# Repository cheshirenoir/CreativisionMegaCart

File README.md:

# CreativisionMegaCart
NOTE: THIS IS NOT COMPATIBLE WITH THE CREATIVISION II WITHOUT MODIFICATION!
(See: http://www.madrigaldesign.it/forum/viewtopic.php?f=10&t=330&p=3201#p3201 )

Multiple ROM Cartridge system for the VTech Creativision, AKA the Dick Smith Wizzard

This is a project I’ve been working on for a while and today I’m pleased to announce the release of our open Source MultiCart system.

Clockmeister kindly gave me all the information from his cart, and gave me permission to release this as Open Source. We both also want to acknowledge and thank the great people over at the Madrigal Design Creativision forums for all their help as well.

My minor contribution was taking the design and putting it in KiCad. I had to spend a bit of time debugging, but Clockmeister assisted above and beyond the call of duty.

This design is released under a CC-BY-SA license. Remix, but always share!

I won’t include ROMs for copyright reasons but they are quite easy to locate on the net if you search around. Note: If you want to program your own EPROM, I understand you have to split the 32K image into two 16K files and then swap the first 16K with the second 16K and re-join them. Clockmeister suggests WinHEX for this.

Parts list is as follows:
1 x 27C801 EPROM (or equivalent)
1 x 0.1uF Ceramic disk capacitor
2 x 1N1418 diode (or equivalent)
1 x DIP switch block (5 switches)
1 x 6 way 4.7kΩ resistor block. (Don’t do what I did and order the 5 way because you counted the pins. It should have seven pins)

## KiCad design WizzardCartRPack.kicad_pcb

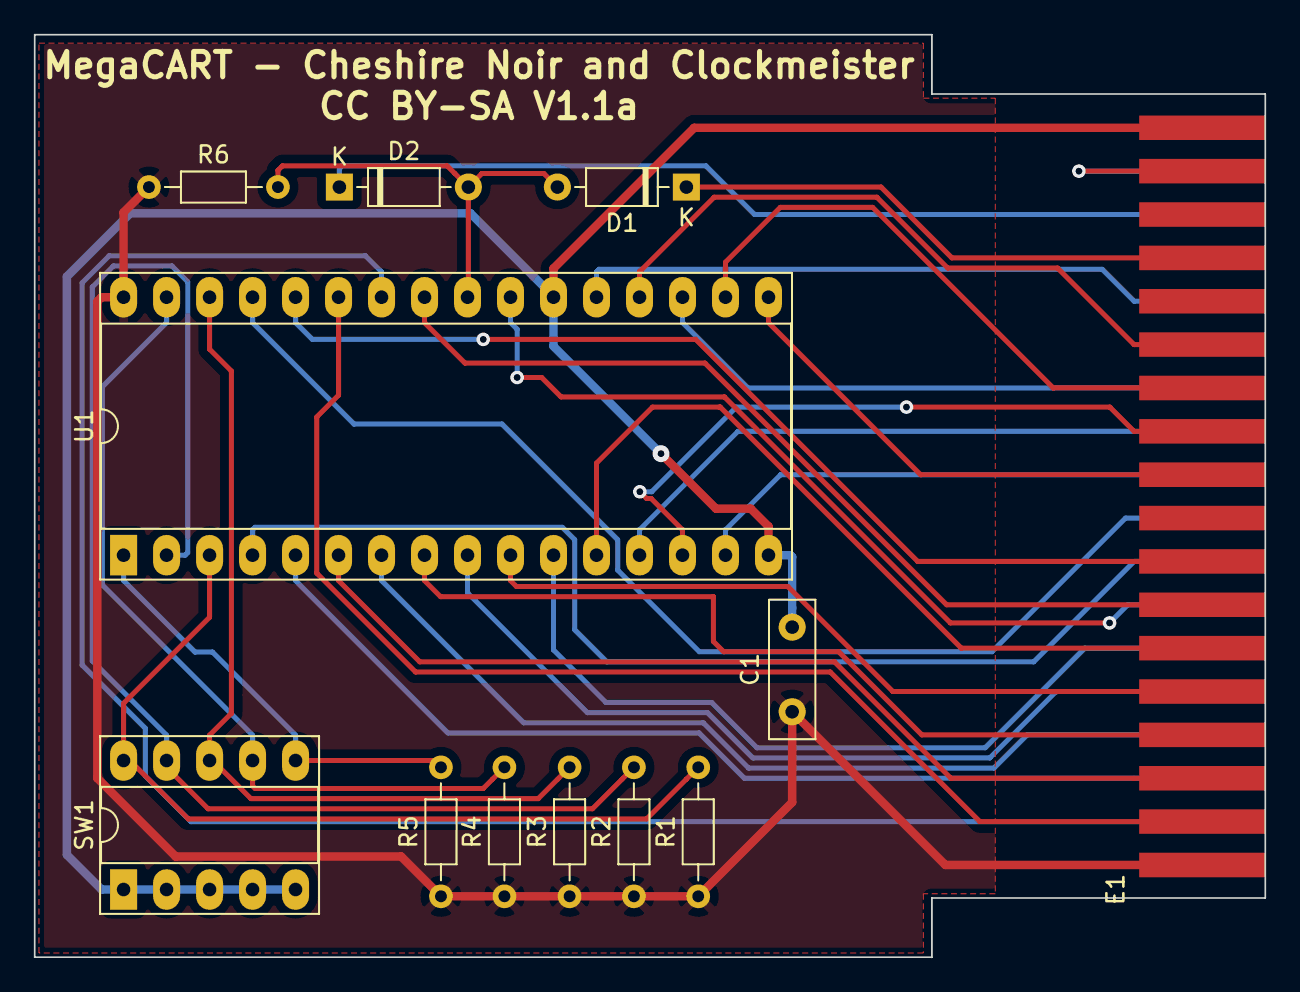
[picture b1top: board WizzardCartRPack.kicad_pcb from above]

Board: 2 copper layers, 72.7 x 54.5 mm, 12 parts (0 on the bottom side), 34 nets.

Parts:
C1: 0.1uF; C_Disc_D8.0mm_W2.5mm_P5.00mm
D1, D2: 1N4148; D_DO-35_SOD27_P7.62mm_Horizontal
E1: 36Edge
R1, R2, R3, R4, R5, R6: 4.7k; R_Axial_DIN0204_L3.6mm_D1.6mm_P7.62mm_Horizontal
SW1: SW_DIP_x05; DIP-10_W7.62mm_Socket_LongPads
U1: 27C801; DIP-32_W15.24mm_Socket_LongPads

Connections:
+5V: C1.1, E1.1, R1.1, R2.1, R3.1, R4.1, R5.1, R6.1, U1.32
GND: C1.2, E1.35, SW1.1, SW1.2, SW1.3, SW1.4, SW1.5, U1.16, U1.22
unnamed: D1.1, E1.29
unnamed: D1.2, D2.2, R6.2, U1.24
unnamed: D2.1, E1.32
unnamed: E1.3, U1.27
unnamed: E1.4, U1.26
unnamed: E1.5, U1.6
unnamed: E1.6, U1.5
unnamed: E1.7, U1.8
unnamed: E1.8, U1.7
unnamed: E1.9, U1.10
unnamed: E1.10, U1.9
unnamed: E1.11, U1.12
unnamed: E1.12, U1.11
unnamed: E1.13, U1.25
unnamed: E1.14, U1.23
unnamed: E1.15, U1.28
unnamed: E1.16, U1.4
unnamed: E1.18, U1.29
unnamed: E1.19, U1.17
unnamed: E1.20, U1.15
unnamed: E1.21, U1.14
unnamed: E1.22, U1.13
unnamed: E1.23, U1.18
unnamed: E1.24, U1.19
unnamed: E1.25, U1.20
unnamed: E1.28, U1.21
unnamed: E1.33, E1.34
unnamed: R1.2, SW1.10, U1.3
unnamed: R2.2, SW1.9, U1.2
unnamed: R3.2, SW1.8, U1.30
unnamed: R4.2, SW1.7, U1.31
unnamed: R5.2, SW1.6, U1.1

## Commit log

2020-10-24 Update README.md
    First cut
2020-10-24 Add files via upload
    Initial upload
2020-10-24 Add files via upload
    Added THIS SIDE UP and mounting holes.
2021-10-31 Update README.md
    It won't work with the CVII
2022-02-04 Add files via upload
    Updated to KiCAD 6.

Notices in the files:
WizzardCartRPack.kicad_pcb:
CC BY-SA V1.1a
